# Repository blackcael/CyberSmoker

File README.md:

# THE CYBERSMOKER
The CyberSmoker has been a 3 year project of practical application of engineering concepts and delicious iteration. With humble beginnings as a weathered, broken down $50 Facebook Marketplace find, it had evolved into a smart IOT device that helps me feed my family and friends at gatherings.

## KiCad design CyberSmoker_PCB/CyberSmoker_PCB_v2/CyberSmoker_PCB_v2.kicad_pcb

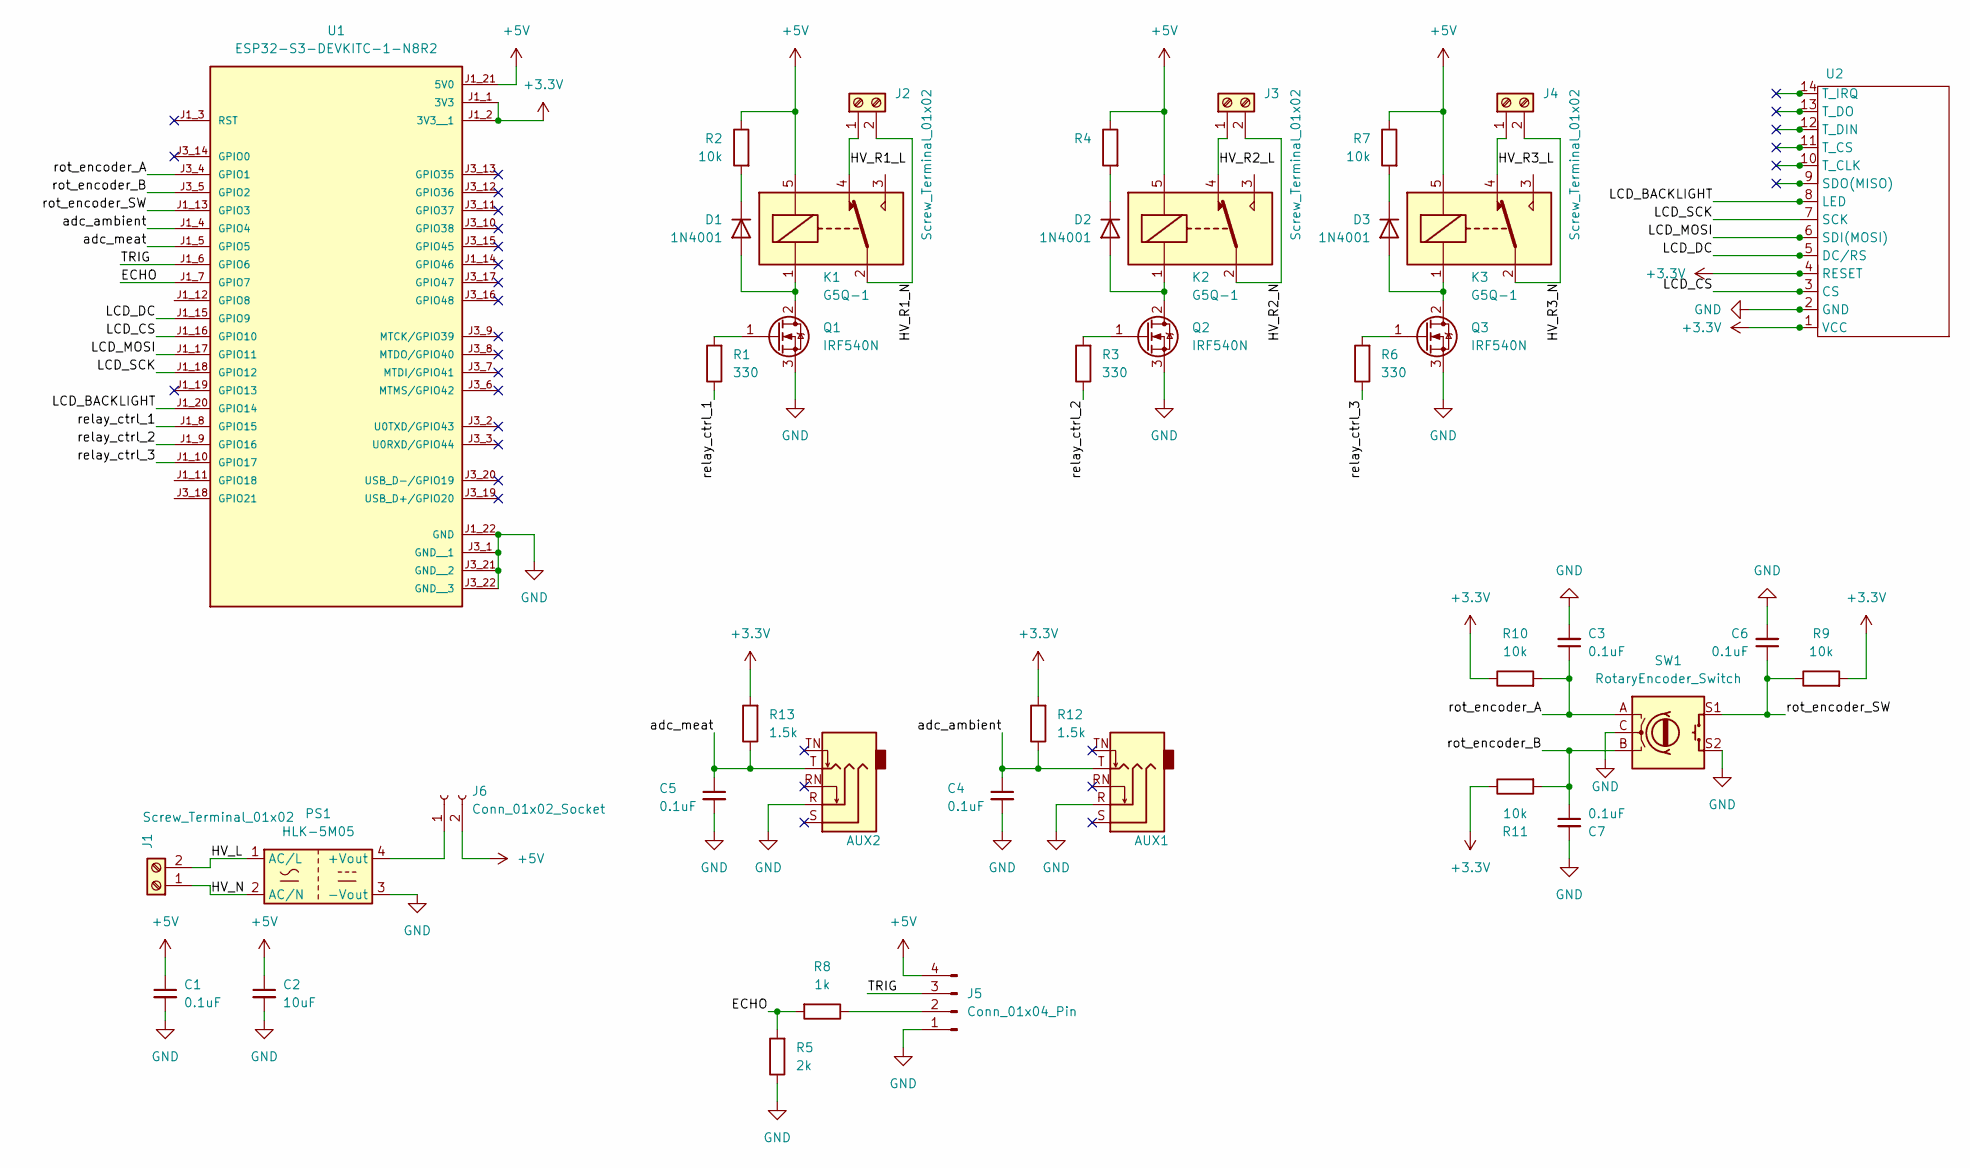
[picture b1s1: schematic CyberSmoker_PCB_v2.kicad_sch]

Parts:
AUX1, AUX2: Jack_3.5mm_CUI_SJ1-3535NG_Horizontal
C1, C3, C4, C5, C6, C7: 0.1uF; C_Disc_D5.1mm_W3.2mm_P5.00mm
C2: 10uF; C_Disc_D5.1mm_W3.2mm_P5.00mm
D1, D2, D3: 1N4001; D_A-405_P7.62mm_Horizontal
J1, J2, J3, J4: Screw_Terminal_01x02; TerminalBlock_bornier-2_P5.08mm
J5: Conn_01x04_Pin; JST_PH_B4B-PH-K_1x04_P2.00mm_Vertical
J6: Conn_01x02_Socket; PinHeader_1x02_P2.54mm_Vertical
K1, K2, K3: G5Q-1; Relay_SPDT_Omron-G5Q-1
PS1: HLK-5M05; Converter_ACDC_Hi-Link_HLK-5Mxx
Q1, Q2, Q3: IRF540N; TO-220-3_Vertical
R1, R3, R6: 330; R_Axial_DIN0207_L6.3mm_D2.5mm_P7.62mm_Horizontal
R2, R4, R7, R9, R10, R11: 10k; R_Axial_DIN0207_L6.3mm_D2.5mm_P7.62mm_Horizontal
R5: 2k; R_Axial_DIN0207_L6.3mm_D2.5mm_P7.62mm_Horizontal
R8: 1k; R_Axial_DIN0207_L6.3mm_D2.5mm_P7.62mm_Horizontal
R12, R13: 1.5k; R_Axial_DIN0207_L6.3mm_D2.5mm_P7.62mm_Horizontal
SW1: RotaryEncoder_Switch; RotaryEncoder_Alps_EC11E-Switch_Vertical_H20mm
U1: ESP32-S3-DEVKITC-1-N8R2; XCVR_ESP32-S3-DEVKITC-1-N8R2; PARTREV V1
U2: LCD_screen

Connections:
+3.3V: R9.2, R10.1, R11.1, R12.2, R13.2, U1.J1_1 (3V3), U1.J1_2 (3V3__1), U2.1 (VCC), U2.4 (RESET)
+5V: C1.1, C2.1, J5.4, J6.2, K1.5, K2.5, K3.5, R2.1, R4.1, R7.1, U1.J1_21 (5V0)
/ECHO: R5.2, R8.2, U1.J1_7 (GPIO7)
/HV_L: J1.2, PS1.1 (AC/L)
/HV_N: J1.1, PS1.2 (AC/N)
/HV_R1_L: J2.1, K1.4
/HV_R1_N: J2.2, K1.2
/HV_R2_L: J3.1, K2.4
/HV_R2_N: J3.2, K2.2
/HV_R3_L: J4.1, K3.4
/HV_R3_N: J4.2, K3.2
/LCD_BACKLIGHT: U1.J1_20 (GPIO14), U2.8 (LED)
/LCD_CS: U1.J1_16 (GPIO10), U2.3 (CS)
/LCD_DC: U1.J1_15 (GPIO9), U2.5 (DC/RS)
/LCD_MOSI: U1.J1_17 (GPIO11), U2.6 (SDI(MOSI))
/LCD_SCK: U1.J1_18 (GPIO12), U2.7 (SCK)
/TRIG: J5.3, U1.J1_6 (GPIO6)
/adc_ambient: AUX1.T, C4.1, R12.1, U1.J1_4 (GPIO4)
/adc_meat: AUX2.T, C5.1, R13.1, U1.J1_5 (GPIO5)
/relay_ctrl_1: R1.1, U1.J1_8 (GPIO15)
/relay_ctrl_2: R3.1, U1.J1_9 (GPIO16)
/relay_ctrl_3: R6.1, U1.J1_10 (GPIO17)
/rot_encoder_A: C3.1, R10.2, SW1.A, U1.J3_4 (GPIO1)
/rot_encoder_B: C7.1, R11.2, SW1.B, U1.J3_5 (GPIO2)
/rot_encoder_SW: C6.1, R9.1, SW1.S1, U1.J1_13 (GPIO3)
GND: AUX1.R, AUX2.R, C1.2, C2.2, C3.2, C4.2, C5.2, C6.2, C7.2, J5.1, PS1.3 (-Vout), Q1.3 (S), Q2.3 (S), Q3.3 (S), R5.1, SW1.C, SW1.S2, U1.J1_22 (GND), U1.J3_1 (GND__1), U1.J3_21 (GND__2), U1.J3_22 (GND__3), U2.2 (GND)
unnamed: D1.2 (A), K1.1, Q1.2 (D)
unnamed: D1.1 (K), R2.2
unnamed: D2.2 (A), K2.1, Q2.2 (D)
unnamed: D2.1 (K), R4.2
unnamed: D3.2 (A), K3.1, Q3.2 (D)
unnamed: D3.1 (K), R7.2
unnamed: J5.2, R8.1
unnamed: J6.1, PS1.4 (+Vout)
unnamed: Q1.1 (G), R1.2
unnamed: Q2.1 (G), R3.2
unnamed: Q3.1 (G), R6.2

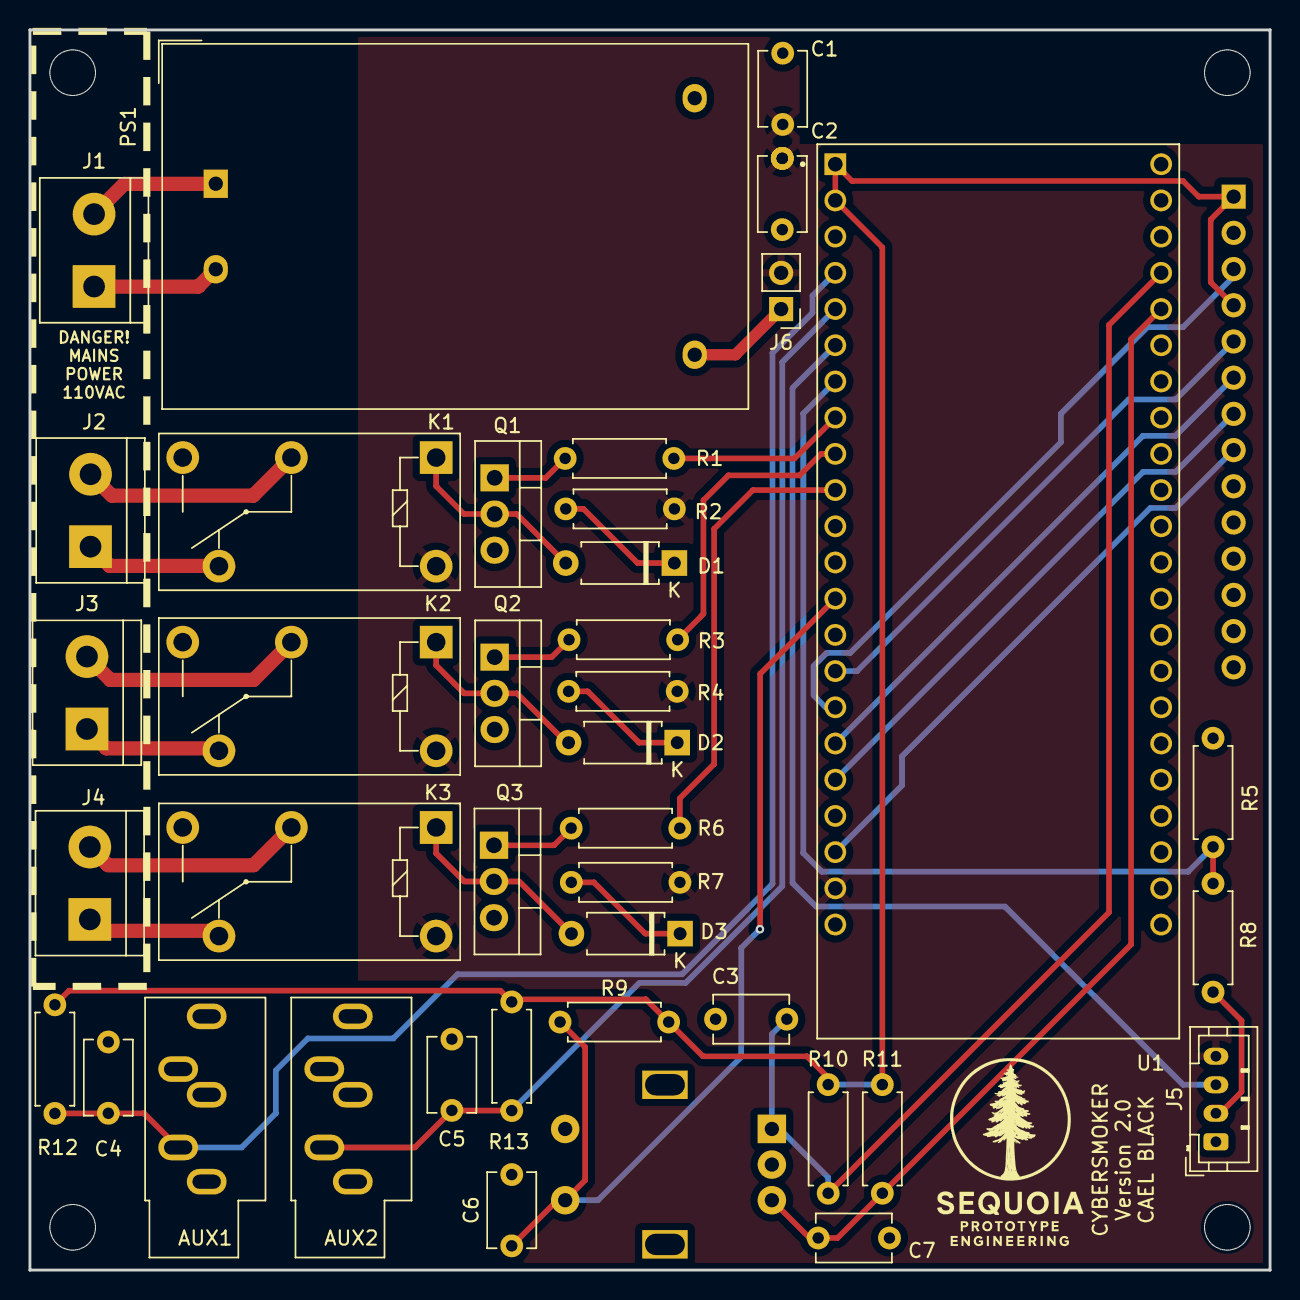
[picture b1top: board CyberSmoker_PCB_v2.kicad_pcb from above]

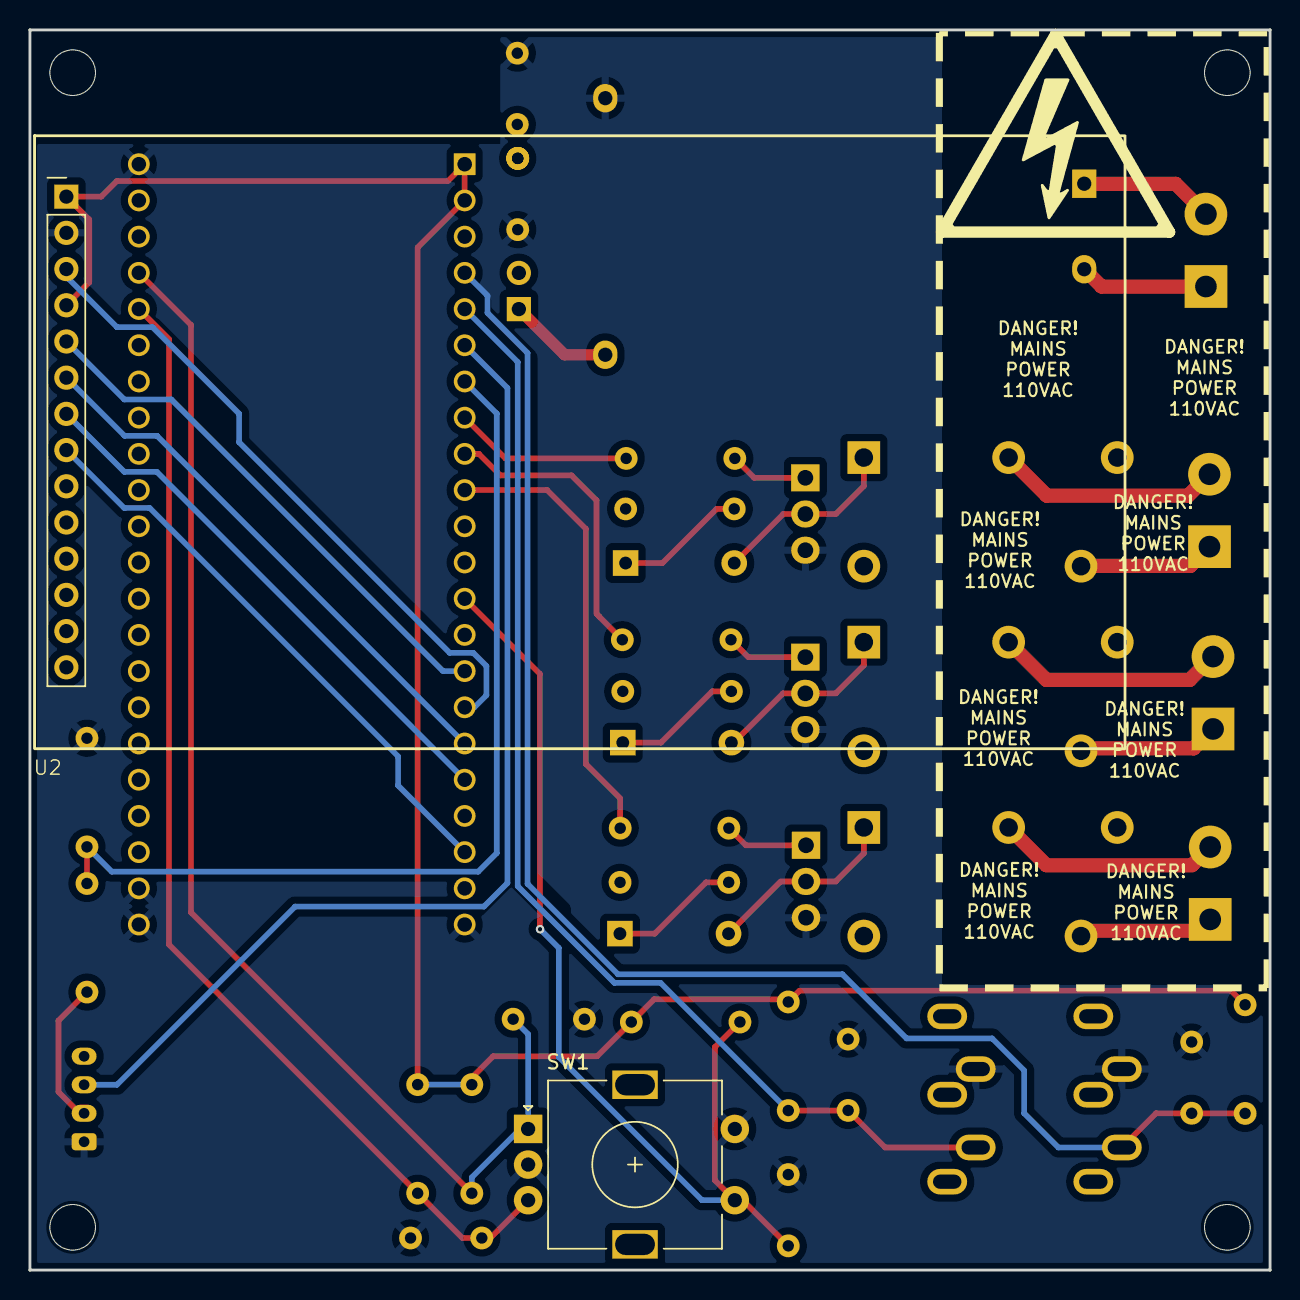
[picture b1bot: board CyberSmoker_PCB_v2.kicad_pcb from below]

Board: 2 copper layers, 87.0 x 87.0 mm, 41 parts (2 on the bottom side), 37 nets.

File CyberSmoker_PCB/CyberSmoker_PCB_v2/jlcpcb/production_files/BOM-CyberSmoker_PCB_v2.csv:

Comment,Designator,Footprint,LCSC,Quantity
0.1uF,C1,C_Disc_D5.1mm_W3.2mm_P5.00mm,,1
10uF,C2,C_Disc_D5.1mm_W3.2mm_P5.00mm,,1
RotaryEncoder_Switch,SW1,RotaryEncoder_Alps_EC11E-Switch_Vertical_H20mm,,1
Conn_01x02_Socket,J6,PinHeader_1x02_P2.54mm_Vertical,,1
~,U2,LCD_screen,,1
ESP32-S3-DEVKITC-1-N8R2,U1,XCVR_ESP32-S3-DEVKITC-1-N8R2,,1
1k,R8,R_Axial_DIN0207_L6.3mm_D2.5mm_P7.62mm_Horizontal,,1
2k,R5,R_Axial_DIN0207_L6.3mm_D2.5mm_P7.62mm_Horizontal,,1
0.1uF,C3,C_Disc_D5.1mm_W3.2mm_P5.00mm,,1
1N4001,D1,D_A-405_P7.62mm_Horizontal,,1
Screw_Terminal_01x02,J1,TerminalBlock_bornier-2_P5.08mm,,1
G5Q-1,K1,Relay_SPDT_Omron-G5Q-1,,1
Screw_Terminal_01x02,J3,TerminalBlock_bornier-2_P5.08mm,,1
IRF540N,Q2,TO-220-3_Vertical,,1
G5Q-1,K2,Relay_SPDT_Omron-G5Q-1,,1
~,AUX1,Jack_3.5mm_CUI_SJ1-3535NG_Horizontal,,1
1.5k,R13,R_Axial_DIN0207_L6.3mm_D2.5mm_P7.62mm_Horizontal,,1
Screw_Terminal_01x02,J4,TerminalBlock_bornier-2_P5.08mm,,1
330,R3,R_Axial_DIN0207_L6.3mm_D2.5mm_P7.62mm_Horizontal,,1
IRF540N,Q1,TO-220-3_Vertical,,1
10k,R10,R_Axial_DIN0207_L6.3mm_D2.5mm_P7.62mm_Horizontal,,1
10k,R4,R_Axial_DIN0207_L6.3mm_D2.5mm_P7.62mm_Horizontal,,1
0.1uF,C4,C_Disc_D5.1mm_W3.2mm_P5.00mm,,1
IRF540N,Q3,TO-220-3_Vertical,,1
10k,R9,R_Axial_DIN0207_L6.3mm_D2.5mm_P7.62mm_Horizontal,,1
~,AUX2,Jack_3.5mm_CUI_SJ1-3535NG_Horizontal,,1
Screw_Terminal_01x02,J2,TerminalBlock_bornier-2_P5.08mm,,1
0.1uF,C7,C_Disc_D5.1mm_W3.2mm_P5.00mm,,1
0.1uF,C6,C_Disc_D5.1mm_W3.2mm_P5.00mm,,1
330,R1,R_Axial_DIN0207_L6.3mm_D2.5mm_P7.62mm_Horizontal,,1
1N4001,D3,D_A-405_P7.62mm_Horizontal,,1
G5Q-1,K3,Relay_SPDT_Omron-G5Q-1,,1
10k,R11,R_Axial_DIN0207_L6.3mm_D2.5mm_P7.62mm_Horizontal,,1
HLK-5M05,PS1,Converter_ACDC_Hi-Link_HLK-5Mxx,,1
10k,R2,R_Axial_DIN0207_L6.3mm_D2.5mm_P7.62mm_Horizontal,,1
0.1uF,C5,C_Disc_D5.1mm_W3.2mm_P5.00mm,,1
Conn_01x04_Pin,J5,JST_PH_B4B-PH-K_1x04_P2.00mm_Vertical,,1
1N4001,D2,D_A-405_P7.62mm_Horizontal,,1
1.5k,R12,R_Axial_DIN0207_L6.3mm_D2.5mm_P7.62mm_Horizontal,,1
330,R6,R_Axial_DIN0207_L6.3mm_D2.5mm_P7.62mm_Horizontal,,1
10k,R7,R_Axial_DIN0207_L6.3mm_D2.5mm_P7.62mm_Horizontal,,1

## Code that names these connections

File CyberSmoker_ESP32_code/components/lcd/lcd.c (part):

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
#define _DEBUG_ 0

#define LCD_MOSI HW_LCD_MOSI
#define LCD_SCLK HW_LCD_SCLK
#define LCD_CS   HW_LCD_CS
#define LCD_DC   HW_LCD_DC
#define LCD_RST  HW_LCD_RST
#define LCD_BL   HW_LCD_BL

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
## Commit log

2026-01-22 Intial Commit
2026-01-22 Add project description to README
    Added project introduction and background information.
2026-01-26 Uploading Documentation
2026-01-27 removed incorrect file
